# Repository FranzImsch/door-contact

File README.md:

# "Dr. Sens" Door Contact

## Features
nRF52832-based magnetic door or window contact. It features a <strong>reed switch</strong> that triggers an interrupt pin of the MCU which then sends a message via <strong>Nordic's ESB protocol</strong> to a gateway. The device is powered by a <strong>CR1632 battery cell</strong>.

The board also serves as breakout for i²c and SPI (pin assignment of nrf52-DK) and a pushbutton that is in parallel to the reed switch is populated. This is for development and makes it possible that the board can <strong>be used as a dashbutton</strong>, for example, as well. There is a TX/RX header as well for easy debugging.

## Software
The software was written using the Arduino-Framework. For communication, the [MySensors Library](https://github.com/mysensors) is being used. The MCU goes to sleep until the interrupt is being triggered. After that, it sends a message (along with the battery charge status) to a gateway. When no ACK is received, the message is resend a set number of times.

## Renderings

## Disclaimer
The board is still in development and I do not guarantee any functionality whatsoever. I do not recommend that you use this device to protect your property.

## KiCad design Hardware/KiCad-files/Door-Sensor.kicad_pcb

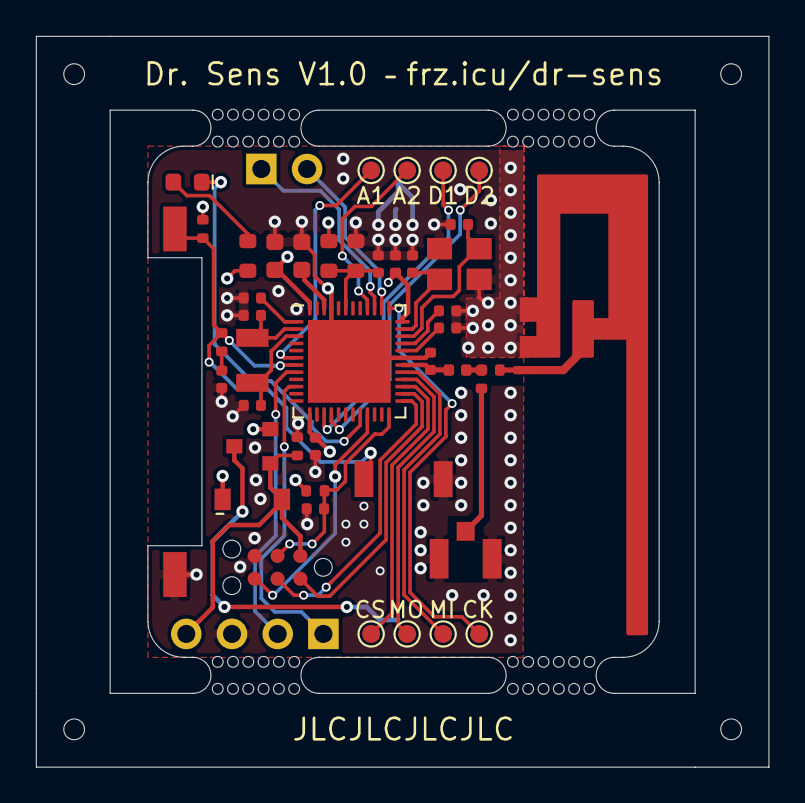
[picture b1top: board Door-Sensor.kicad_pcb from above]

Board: 4 copper layers, 40.7 x 40.6 mm, 51 parts (1 on the bottom side), 37 nets.

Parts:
AE1: Antenna_Shield; Texas_SWRR034C_2.4GHz_Right
BT1: Battery_Cell; BatteryHolder_MYOUNG_BS-16-B4AK003
C1: 10nF; C_0402_1005Metric
C2, C3, C12, C13: 16pF; C_0402_1005Metric
C4, C5, C10, C15: 100nF; C_0402_1005Metric
C6: 4.7µF; C_0603_1608Metric
C7: 1.0µF; C_0603_1608Metric
C8: 100pF; C_0402_1005Metric
C9, C14: DNP; C_0402_1005Metric
C11: 0.8pF; C_0402_1005Metric
D1: D; D_SOD-123
D2: LED PINK; LED_0603_1608Metric
J1: I2C-Conn; PinSocket_1x02_P2.54mm_Vertical
J2: PWR-SERIAL-CONN; PinHeader_1x04_P2.54mm_Vertical
J3: TC2030; Tag-Connect_TC2030-IDC-NL_2x03_P1.27mm_Vertical
J5: U.FL; U.FL_Hirose_U.FL-R-SMT-1_Vertical
L1: 3.9nH; L_0402_1005Metric
Q1: AO3401A; SOT-23
R1: 10kΩ; R_0402_1005Metric
R2: 100kΩ; R_0402_1005Metric
R3: 4.7MΩ; R_0603_1608Metric
R4: 10MΩ; R_0603_1608Metric
R5: 1kΩ; R_0603_1608Metric
R6: 0Ω; R_0402_1005Metric
R7: DNP; R_0402_1005Metric
R8: 1MΩ; R_0402_1005Metric
R9: 1kΩ; R_0402_1005Metric
SW1: SW_Reed; SW_SPST_REED_14.2mm
SW2: SW_SPST; SW_DIP_SPSTx01_Push_TSA343G00-250J2
TP1: A1; TestPoint_Pad_D1.0mm
TP2: D1; TestPoint_Pad_D1.0mm
TP3: D2; TestPoint_Pad_D1.0mm
TP4: CS; TestPoint_Pad_D1.0mm
TP5: MOSI; TestPoint_Pad_D1.0mm
TP6: MISO; TestPoint_Pad_D1.0mm
TP7: A2; TestPoint_Pad_D1.0mm
TP8: SCK; TestPoint_Pad_D1.0mm
U1: nRF52832-QFxx; QFN-48-1EP_6x6mm_P0.4mm_EP4.6x4.6mm
Y1: 32.768kHz; Crystal_SMD_3215-2Pin_3.2x1.5mm
Y2: 32MHz; Crystal_SMD_3225-4Pin_3.2x2.5mm
mouse-bite-2mm-slot, mouse-bite-2mm-slot#2, mouse-bite-2mm-slot#3, mouse-bite-2mm-slot#4: VAL**; mouse-bite-2mm-slot

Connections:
DISABL_BAT: D1.2, J2.4, J3.1, Q1.1, R2.1
GND: AE1.2, BT1.2, C1.1, C2.1, C3.2, C4.2, C5.2, C6.2, C7.1, C8.1, C9.1, C10.1, C11.2, C12.1, C13.1, C14.1, C15.2, J2.3, J3.5, J5.2, R2.2, R4.2, SW1.2, SW2.2, U1.31, U1.45, U1.49, Y2.2
LED: D2.1, U1.20
unnamed: AE1.1, R6.1
unnamed: BT1.1, Q1.3
unnamed: C2.2, U1.2, Y1.1
unnamed: C3.1, U1.3, Y1.2
unnamed: C7.2, U1.46
unnamed: C8.2, U1.33
unnamed: C9.2, U1.32
unnamed: C10.2, U1.1
unnamed: C11.1, L1.1, U1.30
unnamed: C12.2, U1.34, Y2.1
unnamed: C13.2, U1.35, Y2.3
unnamed: C15.1, R9.1
unnamed: D2.2, R5.2
unnamed: J5.1, R7.2
unnamed: L1.2, R6.2, R7.1
unnamed: TP1.1, U1.6
unnamed: TP2.1, U1.15
unnamed: TP3.1, U1.16
unnamed: TP4.1, U1.27
unnamed: TP5.1, U1.28
unnamed: TP6.1, U1.29
unnamed: TP7.1, U1.40
unnamed: TP8.1, U1.37
RESET: C14.2, J3.3, R1.1, U1.24
RX: J2.1, U1.10
SCL: J1.1, U1.39
SDA: J1.2, U1.38
SWDCLK: J3.4, U1.25
SWDIO: J3.2, U1.26
SWO: J3.6, U1.21
TX: J2.2, U1.8
VCC: C4.1, C5.1, C6.1, D1.1, Q1.2, R1.2, R3.1, R5.1, R8.2, U1.13, U1.36, U1.48
V_SENSE: C1.2, R3.2, R4.1, U1.43
WAKEUP: R8.1, R9.2, SW1.1, SW2.1, U1.7

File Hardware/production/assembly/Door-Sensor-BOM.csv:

Comment,Designator,Footprint,LCSC
"Antenna_Shield","AE1","RF_Antenna:Texas_SWRR034C_2.4GHz_Right",""
"Battery_Cell","BT1","Battery:BatteryHolder_MYOUNG_BS-16-B4AK003",""
"10nF","C1","Capacitor_SMD:C_0402_1005Metric","C15195"
"100nF","C4,C5,C10,C15","Capacitor_SMD:C_0402_1005Metric","C1525"
"0.8pF","C11","Capacitor_SMD:C_0402_1005Metric",""
"16pF","C2,C3,C12,C13","Capacitor_SMD:C_0402_1005Metric","C1548"
"4.7µF","C6","Capacitor_SMD:C_0603_1608Metric","C19666"
"1.0µF","C7","Capacitor_SMD:C_0603_1608Metric","C15849"
"100pF","C8","Capacitor_SMD:C_0402_1005Metric","C1546"
"DNP","C9,C14","Capacitor_SMD:C_0402_1005Metric",""
"B5819W","D1","Diode_SMD:D_SOD-123","C8598"
"LED PINK","D2","LED_SMD:LED_0603_1608Metric",""
"I2C-Conn","J1","Connector_PinSocket_2.54mm:PinSocket_1x02_P2.54mm_Vertical",""
"PWR-SERIAL-CONN","J2","Connector_PinHeader_2.54mm:PinHeader_1x04_P2.54mm_Vertical",""
"TC2030","J3","Connector:Tag-Connect_TC2030-IDC-NL_2x03_P1.27mm_Vertical",""
"U.FL","J5","Connector_Coaxial:U.FL_Hirose_U.FL-R-SMT-1_Vertical",""
"3.9nH","L1","Inductor_SMD:L_0402_1005Metric","C14033"
"AO3401A","Q1","Package_TO_SOT_SMD:SOT-23","C15127"
"10kΩ","R1","Resistor_SMD:R_0402_1005Metric","C25744"
"100kΩ","R2","Resistor_SMD:R_0402_1005Metric","C25741"
"4.7MΩ","R3","Resistor_SMD:R_0603_1608Metric","C23163"
"10MΩ","R4","Resistor_SMD:R_0603_1608Metric","C7250"
"1kΩ","R5","Resistor_SMD:R_0603_1608Metric","C21190"
"0Ω","R6","Resistor_SMD:R_0402_1005Metric","C17168"
"DNP","R7","Resistor_SMD:R_0402_1005Metric",""
"1MΩ","R8","Resistor_SMD:R_0402_1005Metric","C26083"
"1kΩ","R9","Resistor_SMD:R_0402_1005Metric","C11702"
"SW_Reed","SW1","Button_Switch_SMD:SW_SPST_REED_14.2mm",""
"SW_SPST","SW2","Button_Switch_SMD:SW_DIP_SPSTx01_Push_TSA343G00-250J2",""
"A1","TP1","TestPoint:TestPoint_Pad_D1.0mm",""
"D1","TP2","TestPoint:TestPoint_Pad_D1.0mm",""
"D2","TP3","TestPoint:TestPoint_Pad_D1.0mm",""
"CS","TP4","TestPoint:TestPoint_Pad_D1.0mm",""
"MOSI","TP5","TestPoint:TestPoint_Pad_D1.0mm",""
"MISO","TP6","TestPoint:TestPoint_Pad_D1.0mm",""
"A2","TP7","TestPoint:TestPoint_Pad_D1.0mm",""
"SCK","TP8","TestPoint:TestPoint_Pad_D1.0mm",""
"nRF52832-QFxx","U1","Package_DFN_QFN:QFN-48-1EP_6x6mm_P0.4mm_EP4.6x4.6mm","C77540"
"32.768kHz","Y1","Crystal:Crystal_SMD_3215-2Pin_3.2x1.5mm","C32346"
"32MHz","Y2","Crystal:Crystal_SMD_3225-4Pin_3.2x2.5mm","C9009"

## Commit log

2021-01-03 initialising repo
2021-01-09 added software
2021-01-09 .DS_Store banished!
